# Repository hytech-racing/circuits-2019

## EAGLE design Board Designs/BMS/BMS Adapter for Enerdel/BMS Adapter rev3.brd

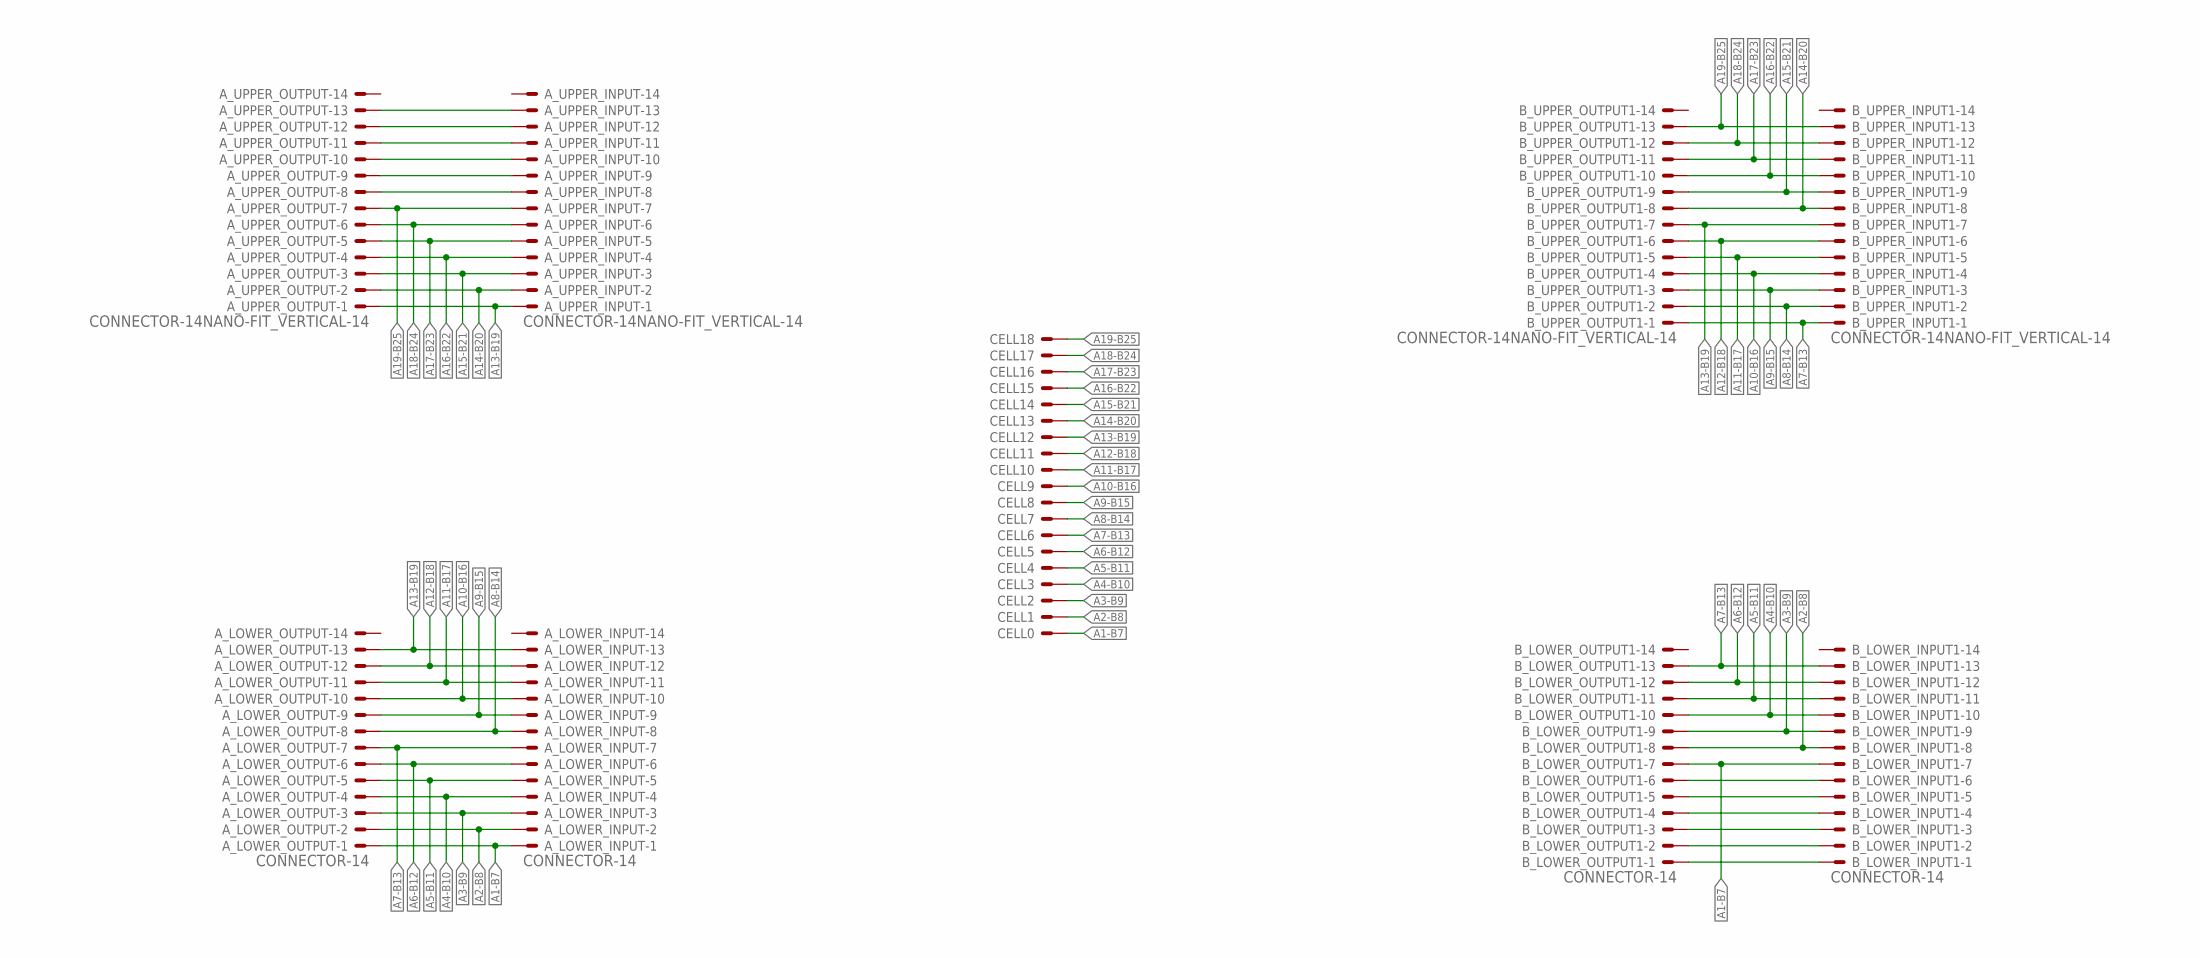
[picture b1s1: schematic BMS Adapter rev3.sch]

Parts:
A_LOWER_INPUT: CONNECTOR-14; MINIFIT_5566-14
A_LOWER_OUTPUT: CONNECTOR-14; MINIFIT_5566-14
A_UPPER_INPUT: CONNECTOR-14NANO-FIT_VERTICAL-14; NANO-FIT_VERTICAL-14
A_UPPER_OUTPUT: CONNECTOR-14NANO-FIT_VERTICAL-14; NANO-FIT_VERTICAL-14
B_LOWER_INPUT1: CONNECTOR-14; MINIFIT_5566-14
B_LOWER_OUTPUT1: CONNECTOR-14; MINIFIT_5566-14
B_UPPER_INPUT1: CONNECTOR-14NANO-FIT_VERTICAL-14; NANO-FIT_VERTICAL-14
B_UPPER_OUTPUT1: CONNECTOR-14NANO-FIT_VERTICAL-14; NANO-FIT_VERTICAL-14
CELL0, CELL1, CELL2, CELL3, CELL4, CELL5, CELL6, CELL7, CELL8, CELL9, CELL10, CELL11, CELL12, CELL13, CELL14, CELL15, CELL16, CELL17, CELL18: BATTERY_SPRING_KEYSTONE5222; KEYSTONE5222

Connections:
A1-B7: A_LOWER_INPUT.1, A_LOWER_OUTPUT.1, B_LOWER_INPUT1.7, B_LOWER_OUTPUT1.7, CELL0.P$1
A2-B8: A_LOWER_INPUT.2, A_LOWER_OUTPUT.2, B_LOWER_INPUT1.8, B_LOWER_OUTPUT1.8, CELL1.P$1
A3-B9: A_LOWER_INPUT.3, A_LOWER_OUTPUT.3, B_LOWER_INPUT1.9, B_LOWER_OUTPUT1.9, CELL2.P$1
A4-B10: A_LOWER_INPUT.4, A_LOWER_OUTPUT.4, B_LOWER_INPUT1.10, B_LOWER_OUTPUT1.10, CELL3.P$1
A5-B11: A_LOWER_INPUT.5, A_LOWER_OUTPUT.5, B_LOWER_INPUT1.11, B_LOWER_OUTPUT1.11, CELL4.P$1
A6-B12: A_LOWER_INPUT.6, A_LOWER_OUTPUT.6, B_LOWER_INPUT1.12, B_LOWER_OUTPUT1.12, CELL5.P$1
A7-B13: A_LOWER_INPUT.7, A_LOWER_OUTPUT.7, B_LOWER_INPUT1.13, B_LOWER_OUTPUT1.13, B_UPPER_INPUT1.P$1, B_UPPER_OUTPUT1.P$1, CELL6.P$1
A8-B14: A_LOWER_INPUT.8, A_LOWER_OUTPUT.8, B_UPPER_INPUT1.P$2, B_UPPER_OUTPUT1.P$2, CELL7.P$1
A9-B15: A_LOWER_INPUT.9, A_LOWER_OUTPUT.9, B_UPPER_INPUT1.P$3, B_UPPER_OUTPUT1.P$3, CELL8.P$1
A10-B16: A_LOWER_INPUT.10, A_LOWER_OUTPUT.10, B_UPPER_INPUT1.P$4, B_UPPER_OUTPUT1.P$4, CELL9.P$1
A11-B17: A_LOWER_INPUT.11, A_LOWER_OUTPUT.11, B_UPPER_INPUT1.P$5, B_UPPER_OUTPUT1.P$5, CELL10.P$1
A12-B18: A_LOWER_INPUT.12, A_LOWER_OUTPUT.12, B_UPPER_INPUT1.P$6, B_UPPER_OUTPUT1.P$6, CELL11.P$1
A13-B19: A_LOWER_INPUT.13, A_LOWER_OUTPUT.13, A_UPPER_INPUT.P$1, A_UPPER_OUTPUT.P$1, B_UPPER_INPUT1.P$7, B_UPPER_OUTPUT1.P$7, CELL12.P$1
A14-B20: A_UPPER_INPUT.P$2, A_UPPER_OUTPUT.P$2, B_UPPER_INPUT1.P$8, B_UPPER_OUTPUT1.P$8, CELL13.P$1
A15-B21: A_UPPER_INPUT.P$3, A_UPPER_OUTPUT.P$3, B_UPPER_INPUT1.P$9, B_UPPER_OUTPUT1.P$9, CELL14.P$1
A16-B22: A_UPPER_INPUT.P$4, A_UPPER_OUTPUT.P$4, B_UPPER_INPUT1.P$10, B_UPPER_OUTPUT1.P$10, CELL15.P$1
A17-B23: A_UPPER_INPUT.P$5, A_UPPER_OUTPUT.P$5, B_UPPER_INPUT1.P$11, B_UPPER_OUTPUT1.P$11, CELL16.P$1
A18-B24: A_UPPER_INPUT.P$6, A_UPPER_OUTPUT.P$6, B_UPPER_INPUT1.P$12, B_UPPER_OUTPUT1.P$12, CELL17.P$1
A19-B25: A_UPPER_INPUT.P$7, A_UPPER_OUTPUT.P$7, B_UPPER_INPUT1.P$13, B_UPPER_OUTPUT1.P$13, CELL18.P$1
A-PASS1: A_UPPER_INPUT.P$8, A_UPPER_OUTPUT.P$8
A-PASS2: A_UPPER_INPUT.P$9, A_UPPER_OUTPUT.P$9
A-PASS3: A_UPPER_INPUT.P$10, A_UPPER_OUTPUT.P$10
A-PASS4: A_UPPER_INPUT.P$11, A_UPPER_OUTPUT.P$11
A-PASS5: A_UPPER_INPUT.P$12, A_UPPER_OUTPUT.P$12
A-PASS6: A_UPPER_INPUT.P$13, A_UPPER_OUTPUT.P$13
B-PASS1: B_LOWER_INPUT1.1, B_LOWER_OUTPUT1.1
B-PASS2: B_LOWER_INPUT1.2, B_LOWER_OUTPUT1.2
B-PASS3: B_LOWER_INPUT1.3, B_LOWER_OUTPUT1.3
B-PASS4: B_LOWER_INPUT1.4, B_LOWER_OUTPUT1.4
B-PASS5: B_LOWER_INPUT1.5, B_LOWER_OUTPUT1.5
B-PASS6: B_LOWER_INPUT1.6, B_LOWER_OUTPUT1.6

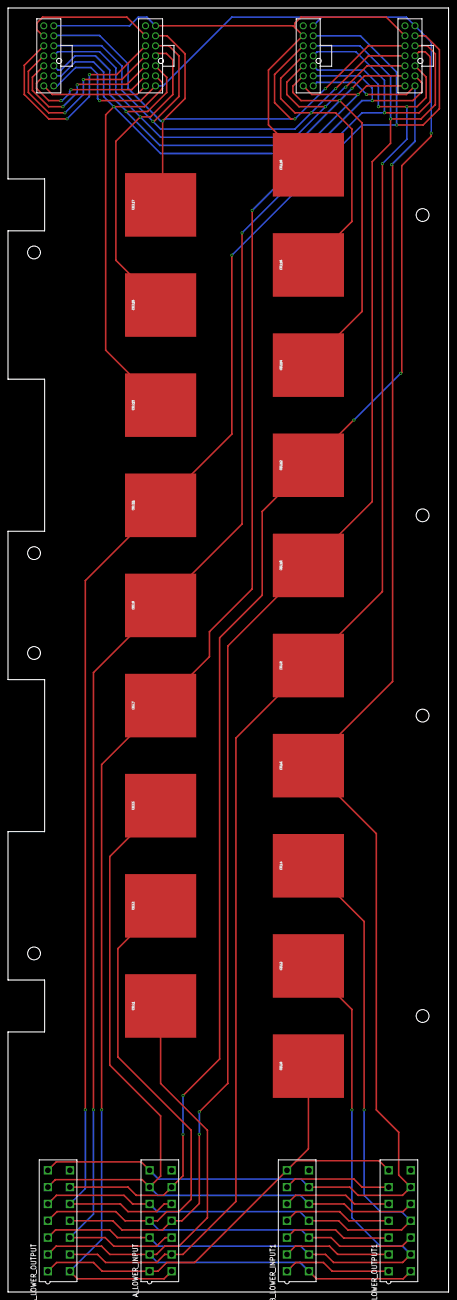
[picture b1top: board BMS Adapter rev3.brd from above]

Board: 2 copper layers, 110.0 x 320.5 mm, 27 parts (0 on the bottom side), 31 nets.

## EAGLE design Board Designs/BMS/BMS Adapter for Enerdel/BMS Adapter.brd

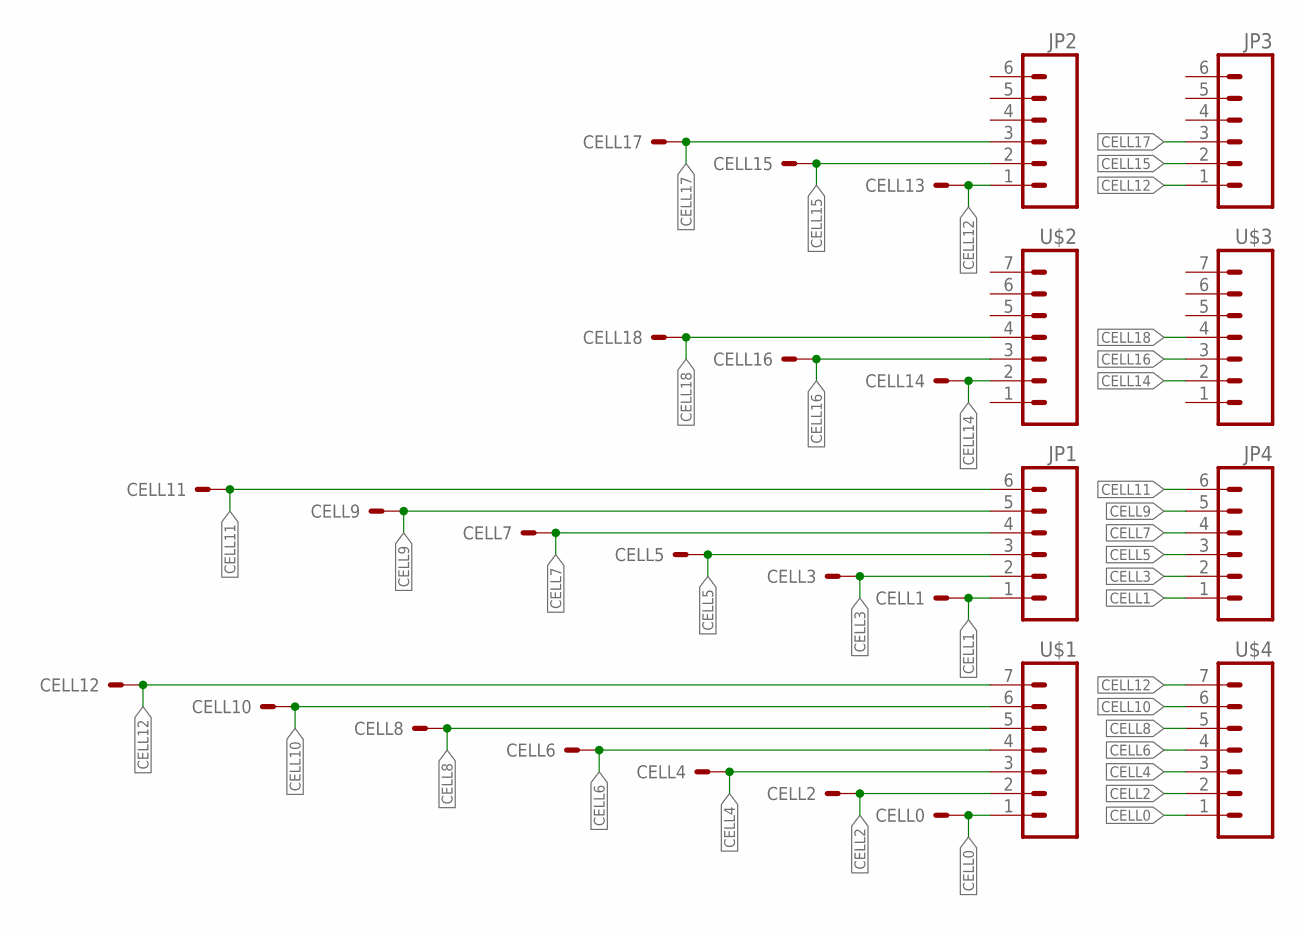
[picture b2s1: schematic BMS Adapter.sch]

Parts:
CELL0, CELL1, CELL2, CELL3, CELL4, CELL5, CELL6, CELL7, CELL8, CELL9, CELL10, CELL11, CELL12, CELL13, CELL14, CELL15, CELL16, CELL17, CELL18: BATTERY_SPRING_KEYSTONE5222; KEYSTONE5222
JP1, JP2, JP3, JP4: M06; 1X06
U$1, U$2, U$3, U$4: M07; 1X07

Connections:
CELL0: CELL0.P$1, U$1.1, U$4.1
CELL1: CELL1.P$1, JP1.1, JP4.1
CELL2: CELL2.P$1, U$1.2, U$4.2
CELL3: CELL3.P$1, JP1.2, JP4.2
CELL4: CELL4.P$1, U$1.3, U$4.3
CELL5: CELL5.P$1, JP1.3, JP4.3
CELL6: CELL6.P$1, U$1.4, U$4.4
CELL7: CELL7.P$1, JP1.4, JP4.4
CELL8: CELL8.P$1, U$1.5, U$4.5
CELL9: CELL9.P$1, JP1.5, JP4.5
CELL10: CELL10.P$1, U$1.6, U$4.6
CELL11: CELL11.P$1, JP1.6, JP4.6
CELL12: CELL12.P$1, CELL13.P$1, JP2.1, JP3.1, U$1.7, U$4.7
CELL14: CELL14.P$1, U$2.2, U$3.2
CELL15: CELL15.P$1, JP2.2, JP3.2
CELL16: CELL16.P$1, U$2.3, U$3.3
CELL17: CELL17.P$1, JP2.3, JP3.3
CELL18: CELL18.P$1, U$2.4, U$3.4

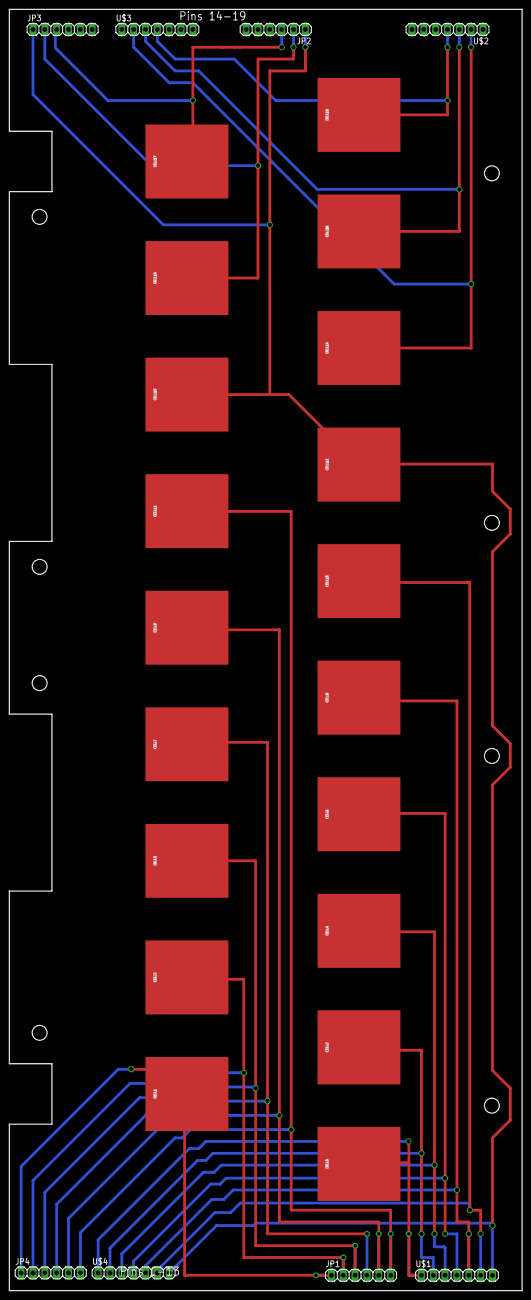
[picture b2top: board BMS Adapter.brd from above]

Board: 2 copper layers, 110.0 x 274.8 mm, 27 parts (0 on the bottom side), 18 nets.

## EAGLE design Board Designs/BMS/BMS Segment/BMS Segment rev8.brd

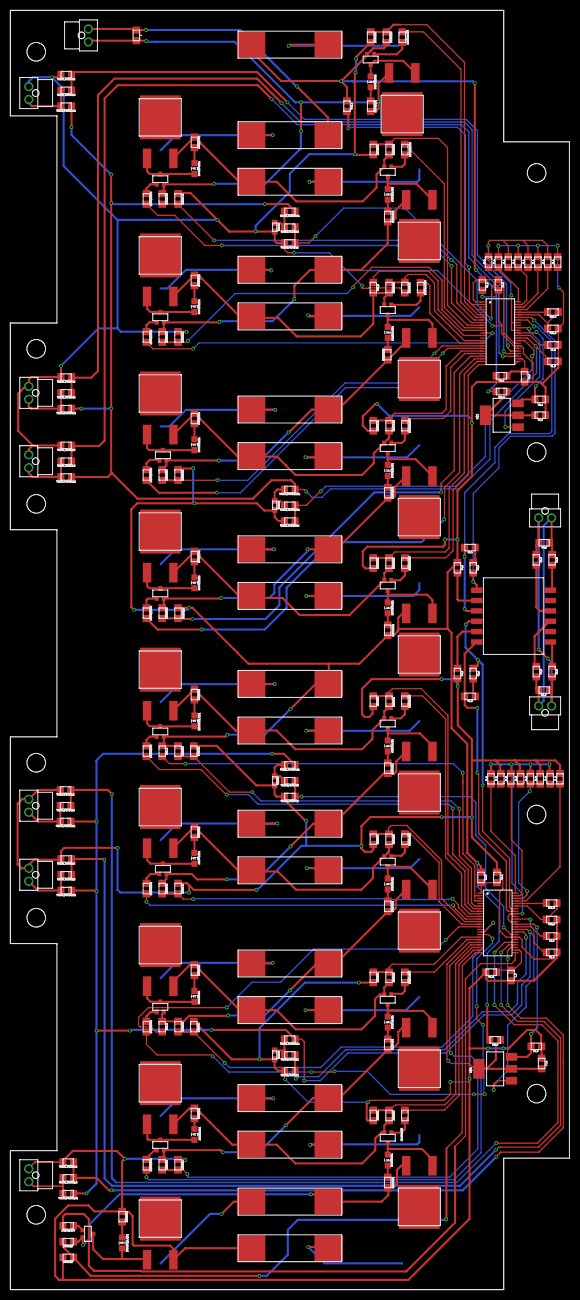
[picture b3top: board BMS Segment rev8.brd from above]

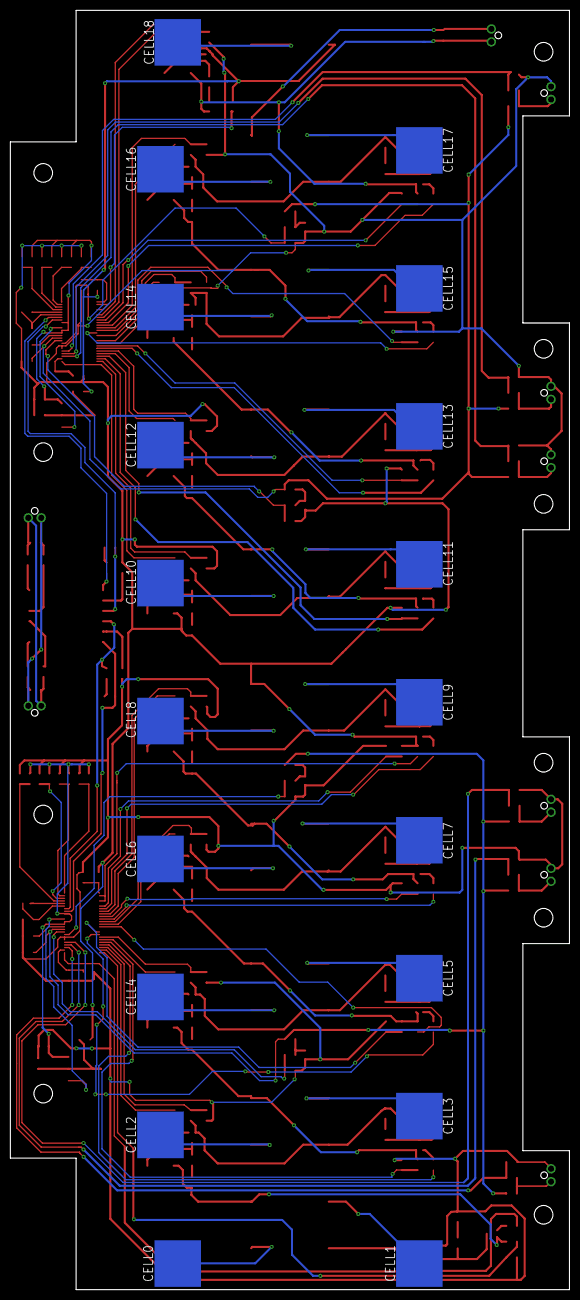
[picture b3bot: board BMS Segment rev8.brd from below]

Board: 2 copper layers, 108.0 x 247.1 mm, 267 parts (19 on the bottom side), 193 nets.

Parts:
AMS_TEST_PORT1: CONNECTOR-2NANO-FIT_VERTICAL-2; NANO-FIT_VERTICAL-2
C1_A, C1_B, C2_A, C2_B, C8_A, C8_B: 1uF; 0805
C3_A, C3_B: 15pF; 0805
C4_A, C4_B, C5_A: 10nF; 0805
C6_A, C6_B, C7_A, C7_B: 0.1uF; 0805
CELL0, CELL1, CELL2, CELL3, CELL4, CELL5, CELL6, CELL7, CELL8, CELL9, CELL10, CELL11, CELL12, CELL13, CELL14, CELL15, CELL16, CELL17, CELL18: BATTERY_SPRING; KEYSTONE5203
C_5: 10nF; 0805
DRAIN1:C, DRAIN2:C, DRAIN3:C, DRAIN4:C, DRAIN5:C, DRAIN6:C, DRAIN7:C, DRAIN8:C, DRAIN9:C, DRAIN10:C, DRAIN11:C, DRAIN12:C, DRAIN13:C, DRAIN14:C, DRAIN15:C, DRAIN16:C, DRAIN17:C, DRAIN18:C: 10nF; 0805
DRAIN1:DISCHARGE, DRAIN2:DISCHARGE, DRAIN3:DISCHARGE, DRAIN4:DISCHARGE, DRAIN5:DISCHARGE, DRAIN6:DISCHARGE, DRAIN7:DISCHARGE, DRAIN8:DISCHARGE, DRAIN9:DISCHARGE, DRAIN10:DISCHARGE, DRAIN11:DISCHARGE, DRAIN12:DISCHARGE, DRAIN13:DISCHARGE, DRAIN14:DISCHARGE, DRAIN15:DISCHARGE, DRAIN16:DISCHARGE, DRAIN17:DISCHARGE, DRAIN18:DISCHARGE: 5R; PWR163
DRAIN1:GATE, DRAIN2:GATE, DRAIN3:GATE, DRAIN4:GATE, DRAIN5:GATE, DRAIN6:GATE, DRAIN7:GATE, DRAIN8:GATE, DRAIN9:GATE, DRAIN10:GATE, DRAIN11:GATE, DRAIN12:GATE, DRAIN13:GATE, DRAIN14:GATE, DRAIN15:GATE, DRAIN16:GATE, DRAIN17:GATE, DRAIN18:GATE: 3K3; 0805
DRAIN1:LED1, DRAIN2:LED1, DRAIN3:LED1, DRAIN4:LED1, DRAIN5:LED1, DRAIN6:LED1, DRAIN7:LED1, DRAIN8:LED1, DRAIN9:LED1, DRAIN10:LED1, DRAIN11:LED1, DRAIN12:LED1, DRAIN13:LED1, DRAIN14:LED1, DRAIN15:LED1, DRAIN16:LED1, DRAIN17:LED1, DRAIN18:LED1: RED; LED-805
DRAIN1:PFET, DRAIN2:PFET, DRAIN3:PFET, DRAIN4:PFET, DRAIN5:PFET, DRAIN6:PFET, DRAIN7:PFET, DRAIN8:PFET, DRAIN9:PFET, DRAIN10:PFET, DRAIN11:PFET, DRAIN12:PFET, DRAIN13:PFET, DRAIN14:PFET, DRAIN15:PFET, DRAIN16:PFET, DRAIN17:PFET, DRAIN18:PFET: P-CHANNEL_MOSFET_DMP3099L-7; SOT23
DRAIN1:R, DRAIN2:R, DRAIN3:R, DRAIN4:R, DRAIN5:R, DRAIN6:R, DRAIN7:R, DRAIN8:R, DRAIN9:R, DRAIN10:R, DRAIN11:R, DRAIN12:R, DRAIN13:R, DRAIN14:R, DRAIN15:R, DRAIN16:R, DRAIN17:R, DRAIN18:R: 100R; 0805
DRAIN1:R1, DRAIN2:R1, DRAIN3:R1, DRAIN4:R1, DRAIN5:R1, DRAIN6:R1, DRAIN7:R1, DRAIN8:R1, DRAIN9:R1, DRAIN10:R1, DRAIN11:R1, DRAIN12:R1, DRAIN13:R1, DRAIN14:R1, DRAIN15:R1, DRAIN16:R1, DRAIN17:R1, DRAIN18:R1: 150R; 0805
F0, F1, F2, F3, F4, F5, F6, F7, F8, F9, F10, F11, F12, F13, F14, F15, F16, F17, F18: 0001.2704.11; 5X20MM_FUSE
ISOSPI_A: CONNECTOR-2NANO-FIT_VERTICAL-2; NANO-FIT_VERTICAL-2
ISOSPI_B: CONNECTOR-2NANO-FIT_VERTICAL-2; NANO-FIT_VERTICAL-2
J, J1_A, J1_B, J2_A, J2_B, J3_A, J3_B, J4_A, J4_B, J5_A, J5_B, J6_A, J6_B, J7_A, J7_B, J8_A, J8_B: 0805
R1_A, R1_B, R2_A, R2_B: 100R; 0805
R3_A, R3_B: 402R; 0805
R4_A, R4_B, R5_A, R5_B: 22R; 0805
RB1_A, RB1_B: 1K2; 0805
RB2_A, RB2_B: 800R; 0805
RIN_A: 100R; 0805
RIN_B: 100R; 0805
RM_A: 100R; 0805
RM_B: 100R; 0805
RU1_A, RU1_B: 100R; 0805
RU2_A, RU2_B: 100Ω; 0805
THERM1, THERM2, THERM3, THERM4: 10K; 0603
THERM1_A, THERM1_B, THERM2_A, THERM2_B, THERM3_A, THERM3_B: Th1; NANO-FIT_VERTICAL-2
THERM_FILTER1:C, THERM_FILTER2:C, THERM_FILTER3:C, THERM_FILTER4:C, THERM_FILTER5:C, THERM_FILTER6:C, THERM_FILTER7:C, THERM_FILTER8:C, THERM_FILTER9:C, THERM_FILTER10:C: 10nF; 0805
THERM_FILTER1:R, THERM_FILTER2:R, THERM_FILTER3:R, THERM_FILTER4:R, THERM_FILTER5:R, THERM_FILTER6:R, THERM_FILTER7:R, THERM_FILTER8:R, THERM_FILTER9:R, THERM_FILTER10:R: 100R; 0805
THERM_FILTER1:R1, THERM_FILTER2:R1, THERM_FILTER3:R1, THERM_FILTER4:R1, THERM_FILTER5:R1, THERM_FILTER6:R1, THERM_FILTER7:R1, THERM_FILTER8:R1, THERM_FILTER9:R1, THERM_FILTER10:R1: 10K; 0805
TRANSFORMER: HM2102NLT
U$1, U$2: LTC6804-2; LTC6804
U$3, U$4: SOT223

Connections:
C0_A: C5_A.1, R2_A.2, U$1.26
C0_B: C_5.1, R2_B.2, U$2.26
C1_A: DRAIN10:C.1, DRAIN10:R.2, U$1.24
C1_B: DRAIN1:C.1, DRAIN1:R.2, U$2.24
C2_A: DRAIN11:C.1, DRAIN11:R.2, U$1.22
C2_B: DRAIN2:C.1, DRAIN2:R.2, U$2.22
C3_A: DRAIN12:C.1, DRAIN12:R.2, U$1.20
C3_B: DRAIN3:C.1, DRAIN3:R.2, U$2.20
C4_A: DRAIN13:C.1, DRAIN13:R.2, U$1.18
C4_B: DRAIN4:C.1, DRAIN4:R.2, U$2.18
C5_A: DRAIN14:C.1, DRAIN14:R.2, U$1.16
C5_B: DRAIN5:C.1, DRAIN5:R.2, U$2.16
C7_A: DRAIN15:C.1, DRAIN15:R.2, U$1.12
C7_B: DRAIN6:C.1, DRAIN6:R.2, U$2.12
C8_A: DRAIN16:C.1, DRAIN16:R.2, U$1.10
C8_B: DRAIN7:C.1, DRAIN7:R.2, U$2.10
C9_A: DRAIN17:C.1, DRAIN17:R.2, U$1.8
C9_B: DRAIN8:C.1, DRAIN8:R.2, U$2.8
C10_A: DRAIN18:C.1, DRAIN18:R.2, U$1.6
C10_B: DRAIN9:C.1, DRAIN9:R.2, U$2.6
CC0: CELL0.P$1, F0.P$1
CC1: CELL1.P$1, F1.P$1
CC2: CELL2.P$1, F2.P$1
CC3: CELL3.P$1, F3.P$1
CC4: CELL4.P$1, F4.P$1
CC5: CELL5.P$1, F5.P$1
CC6: CELL6.P$1, F6.P$1
CC7: CELL7.P$1, F7.P$1
CC8: CELL8.P$1, F8.P$1
CC9: CELL9.P$1, F9.P$1
CC10: CELL10.P$1, F10.P$1
CC11: CELL11.P$1, F11.P$1
CC12: CELL12.P$1, F12.P$1
CC13: CELL13.P$1, F13.P$1
CC14: CELL14.P$1, F14.P$1
CC15: CELL15.P$1, F15.P$1
CC16: CELL16.P$1, F16.P$1
CC17: CELL17.P$1, F17.P$1
CC18: CELL18.P$1, F18.P$1
DRAIN1:GATE: DRAIN1:GATE.1, DRAIN1:PFET.1
DRAIN1:N$1: DRAIN1:DISCHARGE.1, DRAIN1:LED1.A, DRAIN1:PFET.3
DRAIN1:N$2: DRAIN1:LED1.C, DRAIN1:R1.2
DRAIN2:GATE: DRAIN2:GATE.1, DRAIN2:PFET.1
DRAIN2:N$1: DRAIN2:DISCHARGE.1, DRAIN2:LED1.A, DRAIN2:PFET.3
DRAIN2:N$2: DRAIN2:LED1.C, DRAIN2:R1.2
DRAIN3:GATE: DRAIN3:GATE.1, DRAIN3:PFET.1
DRAIN3:N$1: DRAIN3:DISCHARGE.1, DRAIN3:LED1.A, DRAIN3:PFET.3
DRAIN3:N$2: DRAIN3:LED1.C, DRAIN3:R1.2
DRAIN4:GATE: DRAIN4:GATE.1, DRAIN4:PFET.1
DRAIN4:N$1: DRAIN4:DISCHARGE.1, DRAIN4:LED1.A, DRAIN4:PFET.3
DRAIN4:N$2: DRAIN4:LED1.C, DRAIN4:R1.2
DRAIN5:GATE: DRAIN5:GATE.1, DRAIN5:PFET.1
DRAIN5:N$1: DRAIN5:DISCHARGE.1, DRAIN5:LED1.A, DRAIN5:PFET.3
DRAIN5:N$2: DRAIN5:LED1.C, DRAIN5:R1.2
DRAIN6:GATE: DRAIN6:GATE.1, DRAIN6:PFET.1
DRAIN6:N$1: DRAIN6:DISCHARGE.1, DRAIN6:LED1.A, DRAIN6:PFET.3
DRAIN6:N$2: DRAIN6:LED1.C, DRAIN6:R1.2
DRAIN7:GATE: DRAIN7:GATE.1, DRAIN7:PFET.1
DRAIN7:N$1: DRAIN7:DISCHARGE.1, DRAIN7:LED1.A, DRAIN7:PFET.3
DRAIN7:N$2: DRAIN7:LED1.C, DRAIN7:R1.2
DRAIN8:GATE: DRAIN8:GATE.1, DRAIN8:PFET.1
DRAIN8:N$1: DRAIN8:DISCHARGE.1, DRAIN8:LED1.A, DRAIN8:PFET.3
DRAIN8:N$2: DRAIN8:LED1.C, DRAIN8:R1.2
DRAIN9:GATE: DRAIN9:GATE.1, DRAIN9:PFET.1
DRAIN9:N$1: DRAIN9:DISCHARGE.1, DRAIN9:LED1.A, DRAIN9:PFET.3
DRAIN9:N$2: DRAIN9:LED1.C, DRAIN9:R1.2
DRAIN10:GATE: DRAIN10:GATE.1, DRAIN10:PFET.1
DRAIN10:N$1: DRAIN10:DISCHARGE.1, DRAIN10:LED1.A, DRAIN10:PFET.3
DRAIN10:N$2: DRAIN10:LED1.C, DRAIN10:R1.2
DRAIN11:GATE: DRAIN11:GATE.1, DRAIN11:PFET.1
DRAIN11:N$1: DRAIN11:DISCHARGE.1, DRAIN11:LED1.A, DRAIN11:PFET.3
DRAIN11:N$2: DRAIN11:LED1.C, DRAIN11:R1.2
DRAIN12:GATE: DRAIN12:GATE.1, DRAIN12:PFET.1
DRAIN12:N$1: DRAIN12:DISCHARGE.1, DRAIN12:LED1.A, DRAIN12:PFET.3
DRAIN12:N$2: DRAIN12:LED1.C, DRAIN12:R1.2
DRAIN13:GATE: DRAIN13:GATE.1, DRAIN13:PFET.1
DRAIN13:N$1: DRAIN13:DISCHARGE.1, DRAIN13:LED1.A, DRAIN13:PFET.3
DRAIN13:N$2: DRAIN13:LED1.C, DRAIN13:R1.2
DRAIN14:GATE: DRAIN14:GATE.1, DRAIN14:PFET.1
DRAIN14:N$1: DRAIN14:DISCHARGE.1, DRAIN14:LED1.A, DRAIN14:PFET.3
DRAIN14:N$2: DRAIN14:LED1.C, DRAIN14:R1.2
DRAIN15:GATE: DRAIN15:GATE.1, DRAIN15:PFET.1
DRAIN15:N$1: DRAIN15:DISCHARGE.1, DRAIN15:LED1.A, DRAIN15:PFET.3
DRAIN15:N$2: DRAIN15:LED1.C, DRAIN15:R1.2
DRAIN16:GATE: DRAIN16:GATE.1, DRAIN16:PFET.1
DRAIN16:N$1: DRAIN16:DISCHARGE.1, DRAIN16:LED1.A, DRAIN16:PFET.3
DRAIN16:N$2: DRAIN16:LED1.C, DRAIN16:R1.2
DRAIN17:GATE: DRAIN17:GATE.1, DRAIN17:PFET.1
DRAIN17:N$1: DRAIN17:DISCHARGE.1, DRAIN17:LED1.A, DRAIN17:PFET.3
DRAIN17:N$2: DRAIN17:LED1.C, DRAIN17:R1.2
DRAIN18:GATE: DRAIN18:GATE.1, DRAIN18:PFET.1
DRAIN18:N$1: DRAIN18:DISCHARGE.1, DRAIN18:LED1.A, DRAIN18:PFET.3
DRAIN18:N$2: DRAIN18:LED1.C, DRAIN18:R1.2
DRIVE_A: U$1.38, U$3.1
DRIVE_B: U$2.38, U$4.1
GPIO1_A: THERM_FILTER6:C.1, THERM_FILTER6:R.1, U$1.27
GPIO1_B: THERM_FILTER1:C.1, THERM_FILTER1:R.1, U$2.27
GPIO2_A: THERM_FILTER7:C.1, THERM_FILTER7:R.1, U$1.28
GPIO2_B: THERM_FILTER2:C.1, THERM_FILTER2:R.1, U$2.28
GPIO3_A: THERM_FILTER8:C.1, THERM_FILTER8:R.1, U$1.29
GPIO3_B: THERM_FILTER3:C.1, THERM_FILTER3:R.1, U$2.29
GPIO4_A: THERM_FILTER9:C.1, THERM_FILTER9:R.1, U$1.32
GPIO4_B: THERM_FILTER4:C.1, THERM_FILTER4:R.1, U$2.32
GPIO5_A: THERM_FILTER10:C.1, THERM_FILTER10:R.1, U$1.33
GPIO5_B: THERM_FILTER5:C.1, THERM_FILTER5:R.1, U$2.33
IM_A: C3_A.2, TRANSFORMER.P$9, U$1.41
IM_B: C3_B.2, TRANSFORMER.P$12, U$2.41
IP_A: R3_A.1, TRANSFORMER.P$7, U$1.42
IP_B: R3_B.1, TRANSFORMER.P$10, U$2.42
ISOSPI-M: ISOSPI_A.P$2, ISOSPI_B.P$2, R5_A.2, R5_B.2, RM_A.2, RM_B.2
ISOSPI-P: ISOSPI_A.P$1, ISOSPI_B.P$1, R4_A.2, R4_B.2, RM_A.1, RM_B.1
unnamed: C4_B.1, TRANSFORMER.P$11
unnamed: RB1_B.2, U$2.44
unnamed: THERM1_B.P$1, THERM_FILTER1:R.2, THERM_FILTER1:R1.2
unnamed: RB1_B.1, RB2_B.2, U$2.43
unnamed: R4_B.1, TRANSFORMER.P$3
unnamed: RB1_A.2, U$1.44
unnamed: R5_B.1, TRANSFORMER.P$1
unnamed: J7_B.1, J8_B.1, U$2.48
unnamed: J5_B.1, J6_B.1, U$2.47
unnamed: C3_B.1, R3_B.2
unnamed: J3_B.1, J4_B.1, U$2.46
unnamed: J1_B.1, J2_B.1, U$2.45
unnamed: THERM4.2, THERM_FILTER5:R.2, THERM_FILTER5:R1.2
unnamed: THERM2_B.P$1, THERM_FILTER2:R.2, THERM_FILTER2:R1.2
unnamed: THERM3.2, THERM_FILTER4:R.2, THERM_FILTER4:R1.2
unnamed: RB1_A.1, RB2_A.2, U$1.43
unnamed: C4_A.1, TRANSFORMER.P$8
unnamed: R4_A.1, TRANSFORMER.P$6
unnamed: R5_A.1, TRANSFORMER.P$4
unnamed: C3_A.1, R3_A.2
unnamed: THERM3_B.P$1, THERM_FILTER3:R.2, THERM_FILTER3:R1.2
unnamed: J7_A.1, J8_A.1, U$1.48
unnamed: J5_A.1, J6_A.1, U$1.47
unnamed: J3_A.1, J4_A.1, U$1.46
unnamed: J1_A.1, J2_A.1, U$1.45
unnamed: THERM1.2, THERM_FILTER9:R.2, THERM_FILTER9:R1.2
unnamed: THERM3_A.P$1, THERM_FILTER8:R.2, THERM_FILTER8:R1.2
unnamed: THERM2.2, THERM_FILTER10:R.2, THERM_FILTER10:R1.2
unnamed: THERM2_A.P$1, THERM_FILTER7:R.2, THERM_FILTER7:R1.2
unnamed: THERM1_A.P$1, THERM_FILTER6:R.2, THERM_FILTER6:R1.2
S1_A: DRAIN10:GATE.2, U$1.25
S1_B: DRAIN1:GATE.2, U$2.25
S2_A: DRAIN11:GATE.2, U$1.23
S2_B: DRAIN2:GATE.2, U$2.23
S3_A: DRAIN12:GATE.2, U$1.21
S3_B: DRAIN3:GATE.2, U$2.21
S4_A: DRAIN13:GATE.2, U$1.19
S4_B: DRAIN4:GATE.2, U$2.19
S5_A: DRAIN14:GATE.2, U$1.17
S5_B: DRAIN5:GATE.2, U$2.17
S7_A: DRAIN15:GATE.2, U$1.13
S7_B: DRAIN6:GATE.2, U$2.13
S8_A: DRAIN16:GATE.2, U$1.11
S8_B: DRAIN7:GATE.2, U$2.11
S9_A: DRAIN17:GATE.2, U$1.9
S9_B: DRAIN8:GATE.2, U$2.9
S10_A: DRAIN18:GATE.2, U$1.7
S10_B: DRAIN9:GATE.2, U$2.7
SENSE1: DRAIN1:PFET.2, DRAIN1:R.1, DRAIN2:DISCHARGE.2, DRAIN2:R1.1, F1.P$2
SENSE2: DRAIN2:PFET.2, DRAIN2:R.1, DRAIN3:DISCHARGE.2, DRAIN3:R1.1, F2.P$2
SENSE3: DRAIN3:PFET.2, DRAIN3:R.1, DRAIN4:DISCHARGE.2, DRAIN4:R1.1, F3.P$2
SENSE4: DRAIN4:PFET.2, DRAIN4:R.1, DRAIN5:DISCHARGE.2, DRAIN5:R1.1, F4.P$2
SENSE5: DRAIN5:PFET.2, DRAIN5:R.1, DRAIN6:DISCHARGE.2, DRAIN6:R1.1, F5.P$2, RU2_B.1
SENSE6: DRAIN6:PFET.2, DRAIN6:R.1, DRAIN7:DISCHARGE.2, DRAIN7:R1.1, F6.P$2
SENSE7: DRAIN7:PFET.2, DRAIN7:R.1, DRAIN8:DISCHARGE.2, DRAIN8:R1.1, F7.P$2
SENSE8: DRAIN8:PFET.2, DRAIN8:R.1, DRAIN9:DISCHARGE.2, DRAIN9:R1.1, F8.P$2
SENSE10: DRAIN10:PFET.2, DRAIN10:R.1, DRAIN11:DISCHARGE.2, DRAIN11:R1.1, F10.P$2
SENSE11: DRAIN11:PFET.2, DRAIN11:R.1, DRAIN12:DISCHARGE.2, DRAIN12:R1.1, F11.P$2
SENSE12: DRAIN12:PFET.2, DRAIN12:R.1, DRAIN13:DISCHARGE.2, DRAIN13:R1.1, F12.P$2
SENSE13: DRAIN13:PFET.2, DRAIN13:R.1, DRAIN14:DISCHARGE.2, DRAIN14:R1.1, F13.P$2
SENSE14: DRAIN14:PFET.2, DRAIN14:R.1, DRAIN15:DISCHARGE.2, DRAIN15:R1.1, F14.P$2, RU2_A.1
SENSE15: DRAIN15:PFET.2, DRAIN15:R.1, DRAIN16:DISCHARGE.2, DRAIN16:R1.1, F15.P$2
SENSE16: DRAIN16:PFET.2, DRAIN16:R.1, DRAIN17:DISCHARGE.2, DRAIN17:R1.1, F16.P$2
SENSE17: AMS_TEST_PORT1.P$2, DRAIN17:PFET.2, DRAIN17:R.1, DRAIN18:DISCHARGE.2, DRAIN18:R1.1, J.2
SENSE17_J: AMS_TEST_PORT1.P$1, F17.P$2, J.1
SENSE18: DRAIN18:PFET.2, DRAIN18:R.1, F18.P$2, R1_A.1, RIN_A.1, RU1_A.1
UNUSED1_A: RU1_A.2, U$1.2, U$1.4
UNUSED1_B: RU1_B.2, U$2.2, U$2.4
UNUSED2_A: RU2_A.2, U$1.14
UNUSED2_B: RU2_B.2, U$2.14
V+_A: C6_A.1, R1_A.2, U$1.1
V+_B: C6_B.1, R1_B.2, U$2.1
V-_A: C1_A.2, C2_A.2, C4_A.2, C5_A.2, C6_A.2, C7_A.2, C8_A.2, DRAIN9:PFET.2, DRAIN9:R.1, DRAIN10:C.2, DRAIN10:DISCHARGE.2, DRAIN10:R1.1, DRAIN11:C.2, DRAIN12:C.2, DRAIN13:C.2, DRAIN14:C.2, DRAIN15:C.2, DRAIN16:C.2, DRAIN17:C.2, DRAIN18:C.2, F9.P$2, J1_A.2, J3_A.2, J5_A.2, J7_A.2, R1_B.1, R2_A.1, RB2_A.1, RIN_B.1, RU1_B.1, THERM1.1, THERM1_A.P$2, THERM2.1, THERM2_A.P$2, THERM3_A.P$2, THERM_FILTER6:C.2, THERM_FILTER7:C.2, THERM_FILTER8:C.2, THERM_FILTER9:C.2, THERM_FILTER10:C.2, U$1.30, U$1.31
V-_B: C1_B.2, C2_B.2, C4_B.2, C6_B.2, C7_B.2, C8_B.2, C_5.2, DRAIN1:C.2, DRAIN1:DISCHARGE.2, DRAIN1:R1.1, DRAIN2:C.2, DRAIN3:C.2, DRAIN4:C.2, DRAIN5:C.2, DRAIN6:C.2, DRAIN7:C.2, DRAIN8:C.2, DRAIN9:C.2, F0.P$2, J1_B.2, J3_B.2, J5_B.2, J7_B.2, R2_B.1, RB2_B.1, THERM1_B.P$2, THERM2_B.P$2, THERM3.1, THERM3_B.P$2, THERM4.1, THERM_FILTER1:C.2, THERM_FILTER2:C.2, THERM_FILTER3:C.2, THERM_FILTER4:C.2, THERM_FILTER5:C.2, U$2.30, U$2.31
VIN_A: C7_A.1, RIN_A.2, U$3.2, U$3.4
VIN_B: C7_B.1, RIN_B.2, U$4.2, U$4.4
VREF1_A: C2_A.1, U$1.35
VREF1_B: C2_B.1, U$2.35
VREF2_A: C1_A.1, THERM_FILTER6:R1.1, THERM_FILTER7:R1.1, THERM_FILTER8:R1.1, THERM_FILTER9:R1.1, THERM_FILTER10:R1.1, U$1.34
VREF2_B: C1_B.1, THERM_FILTER1:R1.1, THERM_FILTER2:R1.1, THERM_FILTER3:R1.1, THERM_FILTER4:R1.1, THERM_FILTER5:R1.1, U$2.34
VREG_A: C8_A.1, J2_A.2, J4_A.2, J6_A.2, J8_A.2, U$1.36, U$1.37, U$1.40, U$3.3
VREG_B: C8_B.1, J2_B.2, J4_B.2, J6_B.2, J8_B.2, U$2.36, U$2.37, U$2.40, U$4.3

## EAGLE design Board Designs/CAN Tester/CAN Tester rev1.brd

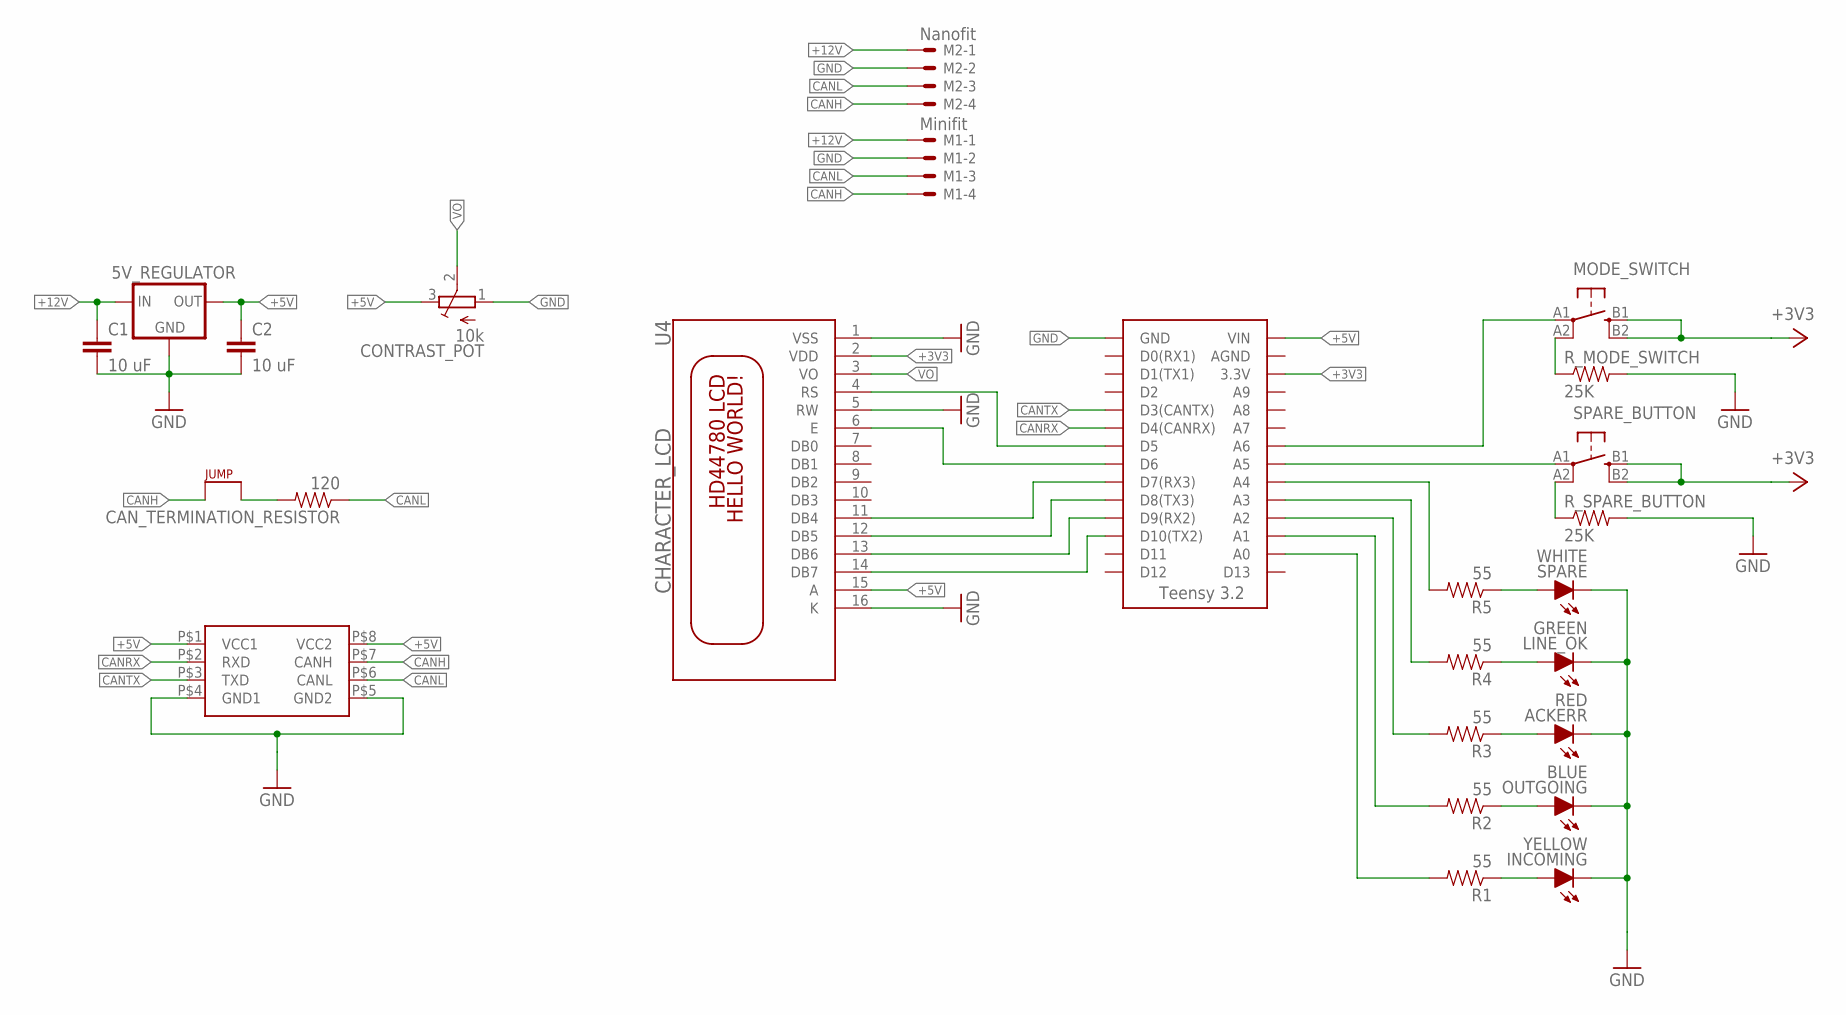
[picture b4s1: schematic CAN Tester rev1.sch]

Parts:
5V_REGULATOR: 5VREG_LM340-NLM340MPX-5.0/NOPB; SOT223
ACKERR: RED; LED-805
C1, C2: 10 uF; 0805
CAN_TERMINATION_RESISTOR: 120; 0805
CONTRAST_POT: 10k; TRIM-3386
INCOMING: YELLOW; LED-805
LINE_OK: GREEN; LED-805
M1: Minifit; DURACLIK_RIGHT_ANGLE-4
M2: Nanofit; NANO-FIT_RIGHT_ANGLE-4-SURFACE
MODE_SWITCH: BTN_10-XXSMD; TACTILE_SWITCH_SMD_6.2MM_TALL
OUTGOING: BLUE; LED-805
R1, R2, R3, R4, R5: 55; 0805
R_MODE_SWITCH: 25K; 0805
R_SPARE_BUTTON: 25K; 0805
SPARE: WHITE; LED-805
SPARE_BUTTON: BTN_10-XXSMD; TACTILE_SWITCH_SMD_6.2MM_TALL
U1: ISOLATED CAN TERMINAL; DUB8
U2: TERMINATION_RESISTOR_JUMPER; 0805
U3: TEENSY_3.2_SIMPLE
U4: CHARACTER_LCD; LCD1602

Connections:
+3V3: MODE_SWITCH.B1 (S), MODE_SWITCH.B2 (S1), SPARE_BUTTON.B1 (S), SPARE_BUTTON.B2 (S1), U3.3.3V, U4.2 (VDD)
+5V: 5V_REGULATOR.3 (OUT), C2.1, CONTRAST_POT.3 (E), U1.P$1 (VCC1), U1.P$8 (VCC2), U3.VIN, U4.15 (A)
+12V: 5V_REGULATOR.1 (IN), C1.1, M1.1, M2.1
CANH: M1.4, M2.4, U1.P$7 (CANH), U2.1
CANL: CAN_TERMINATION_RESISTOR.1, CAN_TERMINATION_RESISTOR.2, M1.3, M2.3, U1.P$6 (CANL), U2.2
CANRX: U1.P$2 (RXD), U3.D4(CANRX)
CANTX: U1.P$3 (TXD), U3.D3(CANTX)
GND: 5V_REGULATOR.2 (GND), 5V_REGULATOR.4 (GND), ACKERR.C, C1.2, C2.2, CONTRAST_POT.1 (A), INCOMING.C, LINE_OK.C, M1.2, M2.2, OUTGOING.C, R_SPARE_BUTTON.2, SPARE.C, U3.GND, U4.5 (RW), U4.16 (K)
unnamed: R1.2, U3.A0
unnamed: R5.1, SPARE.A
unnamed: SPARE_BUTTON.A1, U3.A5
unnamed: R2.2, U3.A1
unnamed: R3.2, U3.A2
unnamed: R4.2, U3.A3
unnamed: R5.2, U3.A4
unnamed: LINE_OK.A, R4.1
unnamed: ACKERR.A, R3.1
unnamed: OUTGOING.A, R2.1
unnamed: INCOMING.A, R1.1
unnamed: R_SPARE_BUTTON.1, SPARE_BUTTON.A2 (P1)
unnamed: MODE_SWITCH.A1, U3.A6
unnamed: MODE_SWITCH.A2 (P1), R_MODE_SWITCH.1
unnamed: U1.P$4 (GND1), U1.P$5 (GND2)
unnamed: U3.D5, U4.4 (RS)
unnamed: U3.D6, U4.6 (E)
unnamed: U3.D7(RX3), U4.11 (DB4)
unnamed: U3.D8(TX3), U4.12 (DB5)
unnamed: U3.D9(RX2), U4.13 (DB6)
unnamed: U3.D10(TX2), U4.14 (DB7)
VO: CONTRAST_POT.2 (S), U4.3 (VO)
VSS: U4.1 (VSS)

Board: 2 copper layers, 25 parts (0 on the bottom side), 30 nets, no tracks yet.

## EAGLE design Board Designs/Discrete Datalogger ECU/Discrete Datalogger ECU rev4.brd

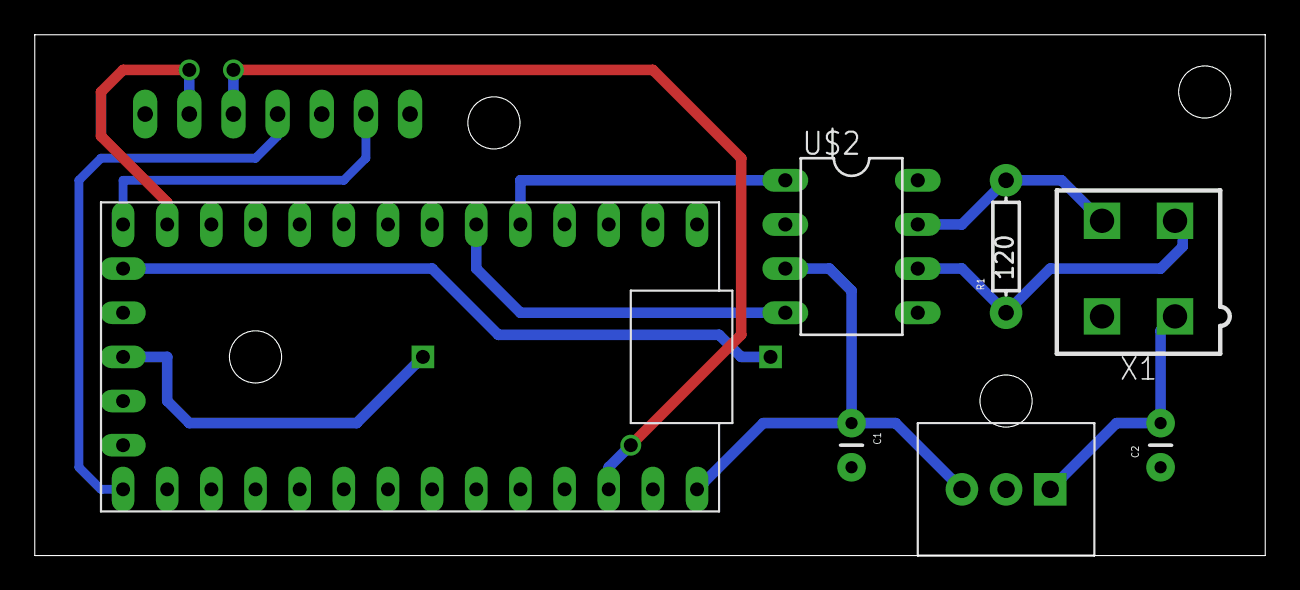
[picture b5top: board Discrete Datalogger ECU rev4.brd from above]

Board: 2 copper layers, 70.8 x 30.0 mm, 9 parts (1 on the bottom side), 13 nets.

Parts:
C1: 0.1uF; CAP-PTH-SMALL
C2: 0.33uF; CAP-PTH-SMALL
IC1: TO-220
R1: 120; AXIAL-0.3
U$1: TEENSY_3.2_EXT
U$2: MCP2551DIL; DIL08
U$3: SDCARD_INTERFACE
U$4: COIN-CELL-HOLDER
X1: CONNECTOR-4; MINIFIT_5566-4

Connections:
12V: C2.2, IC1.1, X1.1
CANH: R1.P$2, U$2.7, X1.4
CANL: R1.P$1, U$2.6, X1.3
GND: C1.2, C2.1, IC1.2, U$1.GND, U$2.2, U$2.8, U$3.CS, U$3.GND, X1.2
unnamed: U$1.VBAT, U$4.VDD
unnamed: U$1.GND2, U$4.GND
unnamed: U$1.D3(CANTX), U$2.1
unnamed: U$1.D4(CANRX), U$2.4
unnamed: U$1.D13, U$3.SCK
unnamed: U$1.D11, U$3.DI
unnamed: U$1.3.3V, U$3.VCC
unnamed: U$1.D12, U$3.DO
VIN: C1.1, IC1.3, U$1.VIN, U$2.3
